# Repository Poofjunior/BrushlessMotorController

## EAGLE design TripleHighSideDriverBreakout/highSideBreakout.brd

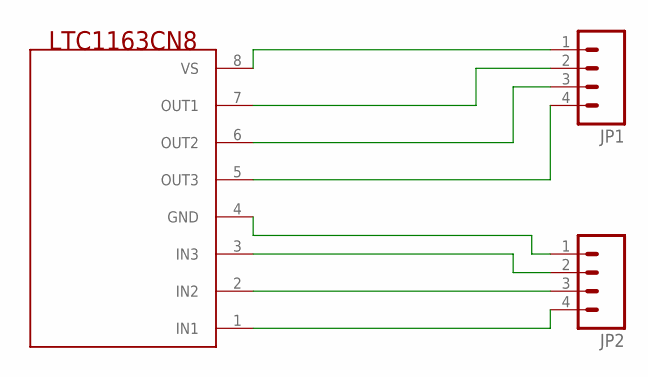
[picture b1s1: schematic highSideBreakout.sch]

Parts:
JP1, JP2: M04PTH; 1X04
U$1: LTC1163CN8; SO08

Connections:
GND: JP2.1, U$1.4 (GND)
unnamed: JP2.4, U$1.1 (IN1)
unnamed: JP2.3, U$1.2 (IN2)
unnamed: JP2.2, U$1.3 (IN3)
unnamed: JP1.4, U$1.5 (OUT3)
unnamed: JP1.3, U$1.6 (OUT2)
unnamed: JP1.2, U$1.7 (OUT1)
unnamed: JP1.1, U$1.8 (VS)

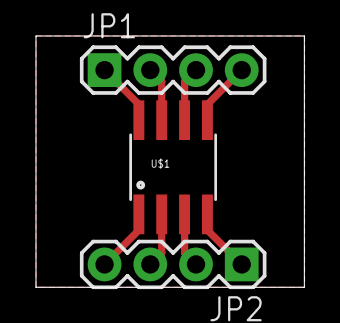
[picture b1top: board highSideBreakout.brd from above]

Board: 2 copper layers, 14.9 x 14.0 mm, 3 parts (0 on the bottom side), 8 nets.

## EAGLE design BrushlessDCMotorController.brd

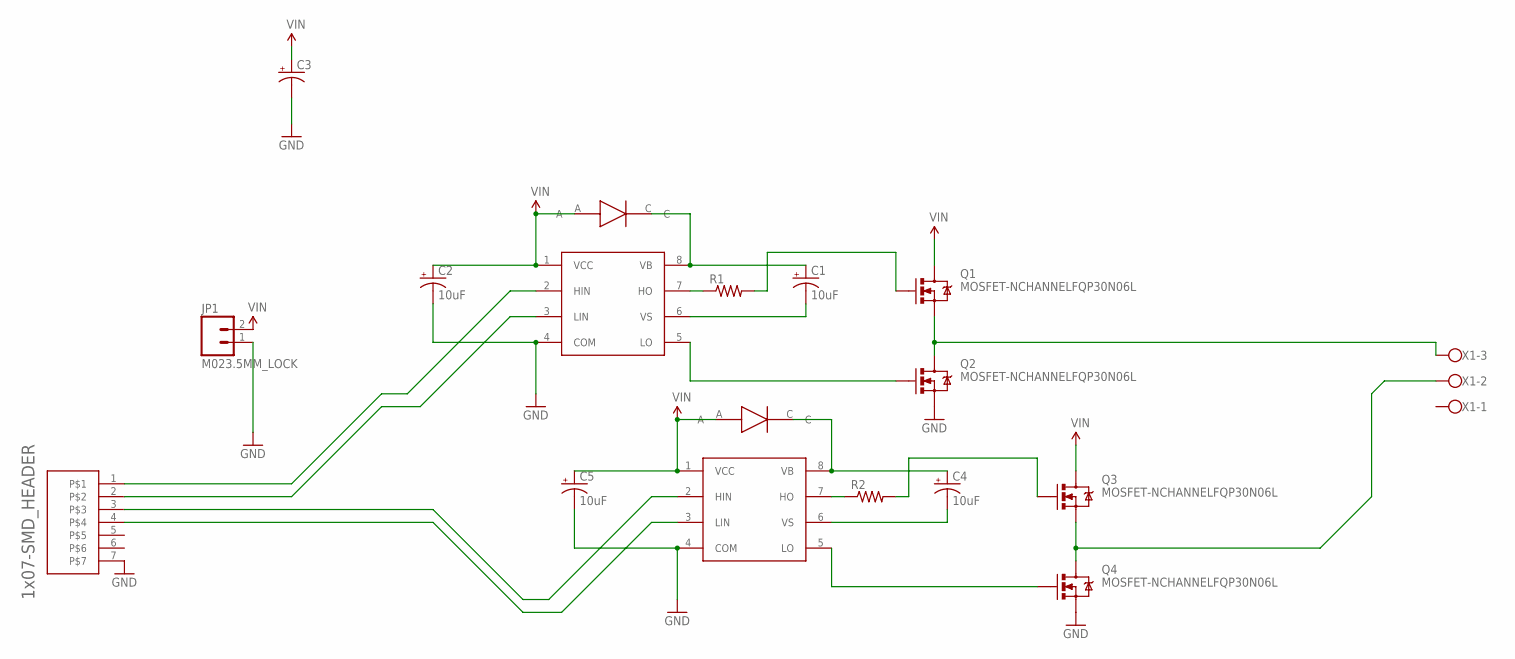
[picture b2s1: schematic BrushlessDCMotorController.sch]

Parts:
C1, C2, C4, C5: 10uF; EIA3216
C3: CAP_POLD; PANASONIC_D
JP1: M023.5MM_LOCK; SCREWTERMINAL-3.5MM-2_LOCK
Q1, Q2, Q3, Q4: MOSFET-NCHANNELFQP30N06L; TO220V
R1, R2: RESISTOR0805-RES; 0805
U$1, U$4: IR2101; SO08
U$2, U$5: DFLS1150; 2SMD_FLAT_LEAD
U$3: 1X07-SMD_HEADER
X1: W239-103

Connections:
GND: C2.C (-), C3.-, C5.C (-), JP1.1, Q2.3 (S), Q4.3 (S), U$1.4 (COM), U$3.7, U$4.4 (COM)
unnamed: C1.A (+), U$1.8 (VB), U$2.C
unnamed: C1.C (-), U$1.6 (VS)
unnamed: Q2.1 (G), U$1.5 (LO)
unnamed: U$1.2 (HIN), U$3.1
unnamed: R1.1, U$1.7 (HO)
unnamed: Q1.1 (G), R1.2
unnamed: Q1.3 (S), Q2.2 (D), X1.3
unnamed: U$1.3 (LIN), U$3.2
unnamed: C4.A (+), U$4.8 (VB), U$5.C
unnamed: C4.C (-), U$4.6 (VS)
unnamed: R2.1, U$4.7 (HO)
unnamed: Q3.1 (G), R2.2
unnamed: Q3.3 (S), Q4.2 (D), X1.2
unnamed: Q4.1 (G), U$4.5 (LO)
unnamed: U$3.3, U$4.2 (HIN)
unnamed: U$3.4, U$4.3 (LIN)
VIN: C2.A (+), C3.+, C5.A (+), JP1.2, Q1.2 (D), Q3.2 (D), U$1.1 (VCC), U$2.A, U$4.1 (VCC), U$5.A

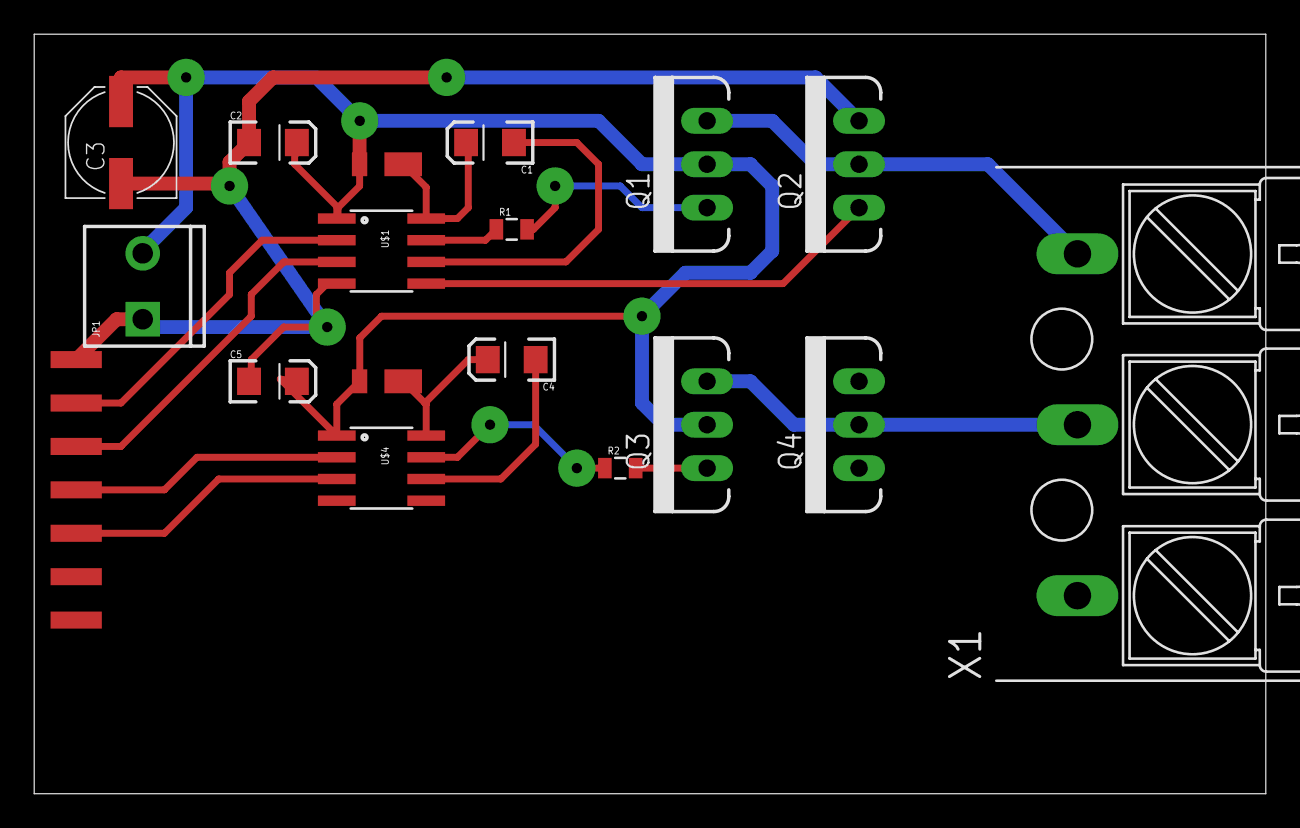
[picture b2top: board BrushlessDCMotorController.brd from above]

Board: 2 copper layers, 72.1 x 44.4 mm, 18 parts (0 on the bottom side), 18 nets.

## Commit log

2014-01-12 added PCB fils

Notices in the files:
parts and their libraries:
SparkFun-Connectors: Licensing: CC v3.0 Share-Alike You are welcome to use this library for commercial purposes.
